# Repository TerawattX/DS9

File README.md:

# Model_DS9
  This project contains notes, code, and schematic files for the lighting and control circuitry for my build of the AMT Deep Space 9 model kit.
  
- [Model\_DS9](#model_ds9)
  - [File elements](#file-elements)
    - [Deep Space Nine](#deep-space-nine)
    - [Arduino](#arduino)
    - [Eagle CAD](#eagle-cad)
- [Hardware Required](#hardware-required)
  - [Assembly Instructions](#assembly-instructions)

## File elements

### Deep Space Nine
OneNote document containing various design and build notes.

### Arduino
Arduino code for the primary control board.

### Eagle CAD
Circuit diagrams and printed circuit board schematics for control components.

# Hardware Required

## Assembly Instructions

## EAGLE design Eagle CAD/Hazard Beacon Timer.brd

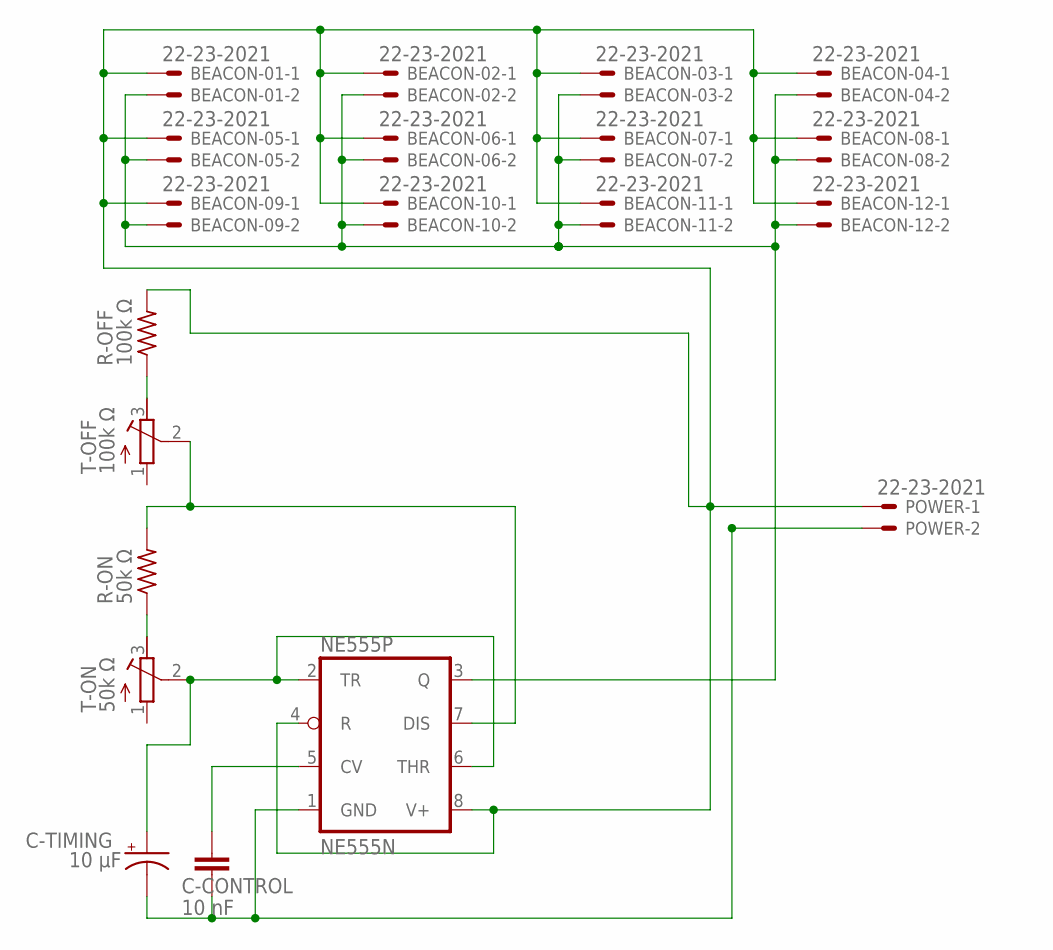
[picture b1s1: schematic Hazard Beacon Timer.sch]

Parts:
BEACON-01, BEACON-02, BEACON-03, BEACON-04, BEACON-05, BEACON-06, BEACON-07, BEACON-08, BEACON-09, BEACON-10, BEACON-11, BEACON-12: 22-23-2021
C-CONTROL: 10 nF; C2.5-2
C-TIMING: 10 μF; E2-5
NE555P: NE555N; DIL08
POWER: 22-23-2021
R-OFF: 100k Ω; 0207/7
R-ON: 50k Ω; 0207/7
T-OFF: 100k Ω; RTRIM5X
T-ON: 50k Ω; RTRIM5X

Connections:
unnamed: C-CONTROL.1, NE555P.5 (CV)
unnamed: R-ON.1, T-ON.3 (E)
unnamed: NE555P.7 (DIS), R-ON.2, T-OFF.2 (S)
unnamed: BEACON-01.1, BEACON-02.1, BEACON-03.1, BEACON-04.1, BEACON-05.1, BEACON-06.1, BEACON-07.1, BEACON-08.1, BEACON-09.1, BEACON-10.1, BEACON-11.1, BEACON-12.1, NE555P.4 (R), NE555P.8 (V+), POWER.1, R-OFF.2
unnamed: R-OFF.1, T-OFF.3 (E)
unnamed: BEACON-01.2, BEACON-02.2, BEACON-03.2, BEACON-04.2, BEACON-05.2, BEACON-06.2, BEACON-07.2, BEACON-08.2, BEACON-09.2, BEACON-10.2, BEACON-11.2, BEACON-12.2, NE555P.3 (Q)
unnamed: C-TIMING.+, NE555P.2 (TR), NE555P.6 (THR), T-ON.2 (S)
unnamed: C-CONTROL.2, C-TIMING.-, NE555P.1 (GND), POWER.2

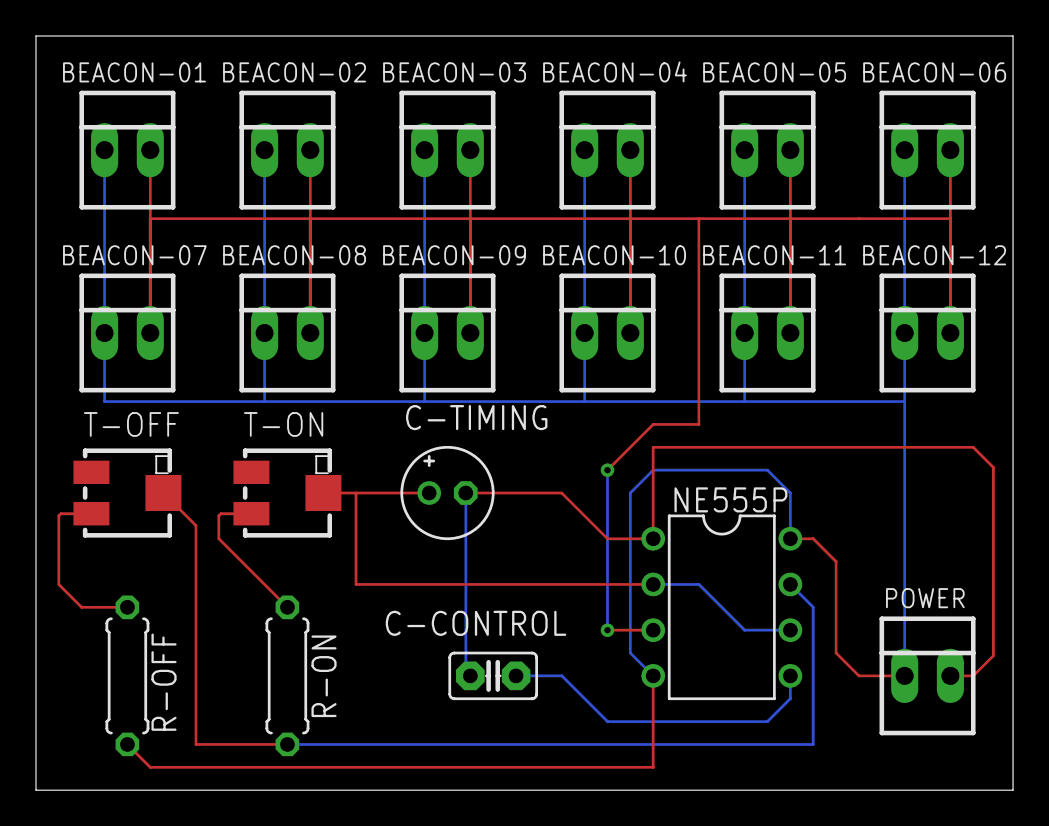
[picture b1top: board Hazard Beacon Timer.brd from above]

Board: 2 copper layers, 54.3 x 41.9 mm, 20 parts (0 on the bottom side), 8 nets.

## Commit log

2023-03-31 Initial Commit.
    Add basic schematic and board file.
2023-03-31 Beacon Control Board update
    - Rename Schematic to Hazard Beacon Timer since there are going to be other components/boards.
    - Update board diagram to a more final layout.
2023-03-31 Add OneNote file for notes
2023-03-31 Reorg Files
    - Reorganized files into directories
    - Add ReadMe contents
    - Add notes to OneNote
2023-04-13 Update to notes
2023-04-15 3d print testing
2023-04-16 Update print notes
2023-04-23 Print test updates
2023-06-01 Update to print status
